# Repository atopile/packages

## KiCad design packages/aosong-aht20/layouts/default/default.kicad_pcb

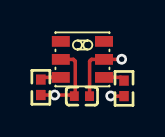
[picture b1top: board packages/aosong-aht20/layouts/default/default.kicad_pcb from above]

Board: 2 copper layers, 4 parts (0 on the bottom side), 4 nets.

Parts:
C1: 1F; C0402
R1, R2: 10000Ω; R0402
U1: SENSOR-SMD-6_AHT20

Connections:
SCL: R1.2, U1.3
SDA: R2.2, U1.4
hv: C1.1, R1.1, R2.1, U1.2
lv: C1.2, U1.5

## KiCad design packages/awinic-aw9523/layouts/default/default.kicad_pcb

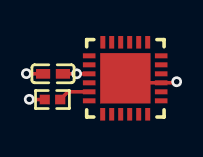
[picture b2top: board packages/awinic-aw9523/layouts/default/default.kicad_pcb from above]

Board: 2 copper layers, 3 parts (0 on the bottom side), 3 nets.

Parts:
C1: 100nF; C0402
R1: 10kΩ; R0402
U1: VFQFPN-24_L4.0-W4.0-P0.50-BL-EP2.8

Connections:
RSTN: R1.1, U1.23
hv: C1.1, U1.21
lv: C1.2, R1.2, U1.9, U1.18, U1.24, U1.25

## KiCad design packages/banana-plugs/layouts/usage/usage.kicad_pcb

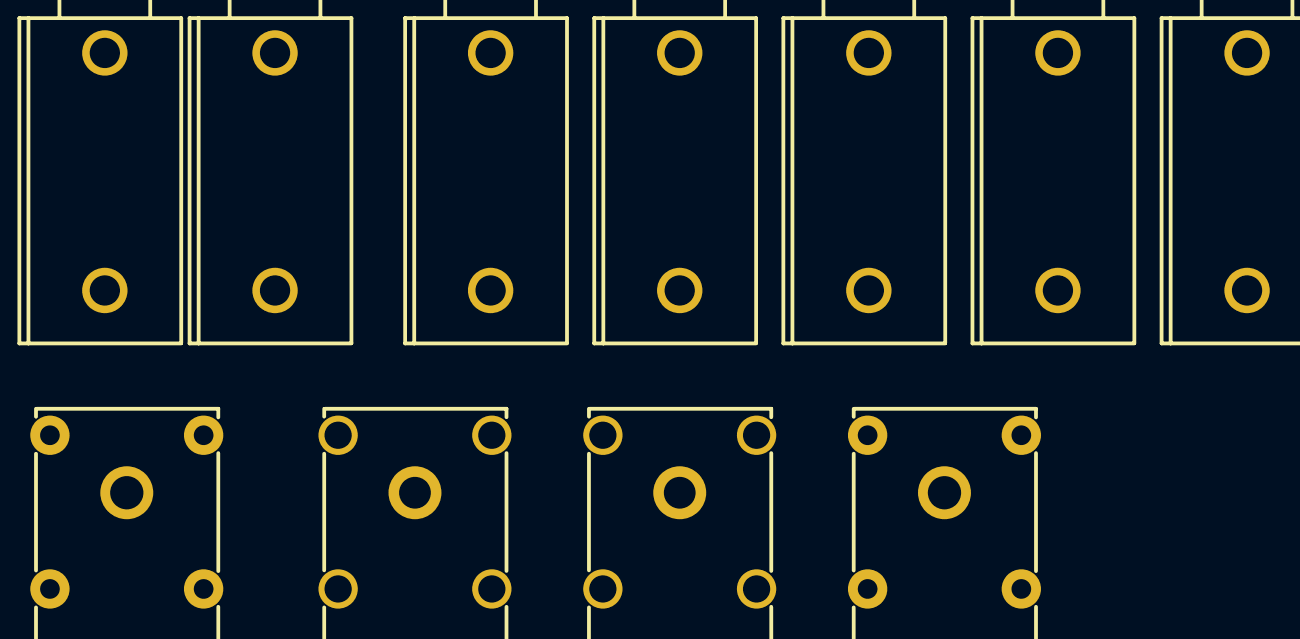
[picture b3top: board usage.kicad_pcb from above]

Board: 2 copper layers, 11 parts (0 on the bottom side), 2 nets, no tracks yet.

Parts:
J1, J2: ANT-TH_L33.0-W12.0_BLACK
J3, J4: ANT-TH_L33.0-W12.0_RED
J5, J6, J7, J8, J11: CONN-TH_24.243.2
J9, J10: CONN-TH_24.243.1_RED

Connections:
hv: J1.1, J1.2, J3.1, J3.2, J4.1, J4.2, J5.1, J5.2, J6.1, J6.2, J7.1, J7.2, J9.1, J9.2, J10.1, J10.2, J11.1, J11.2
lv: J2.1, J2.2, J8.1, J8.2
